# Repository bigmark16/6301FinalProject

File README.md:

# 6301FinalProject
the final project for 6.301. The files included are the eagle schematic file and the brd file used for pcb fab.

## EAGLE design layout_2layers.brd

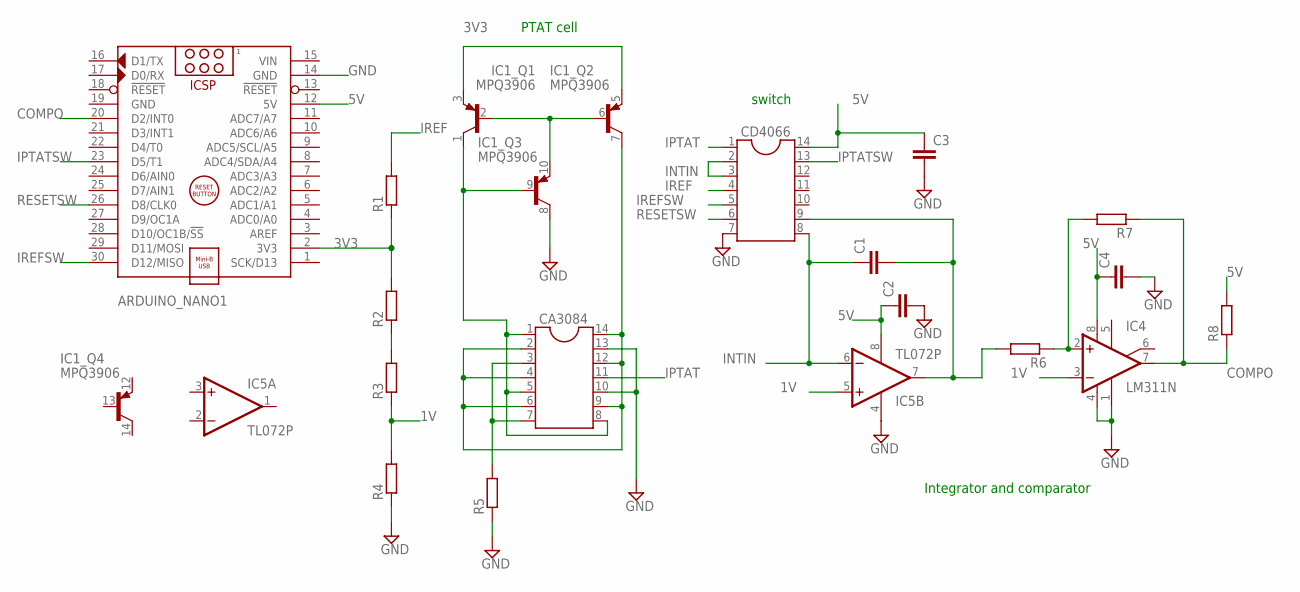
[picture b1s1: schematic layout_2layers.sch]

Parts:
ARDUINO_NANO1: ARDUINO_NANO
C1, C2, C3, C4: C-EU050-025X075; C050-025X075
CA3084: DIL14S; SOCKET-14
CD4066: DIL14S; SOCKET-14
IC1: MPQ3906; DIL14
IC4: LM311N; DIL08
IC5: TL072P; DIL08
R1, R2, R3, R4, R5, R6, R7, R8: R-EU_0207/10; 0207/10

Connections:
1V: IC4.3 (-IN), IC5.5 (+IN), R3.1, R4.2
3V3: ARDUINO_NANO1.2 (3V3), IC1.3 (E), IC1.5 (E), R1.1, R2.2
5V: ARDUINO_NANO1.12 (5V), C2.1, C3.1, C4.1, CD4066.14, IC4.8 (V+), IC5.8 (V+), R8.2
COMPO: ARDUINO_NANO1.20 (D2/INT0), IC4.7 (OUT), R7.1, R8.1
GND: ARDUINO_NANO1.14 (GND), ARDUINO_NANO1.19 (GND), C2.2, C3.2, C4.2, CA3084.10, CA3084.13, CD4066.7, IC1.8 (C), IC4.1 (GND), IC4.4 (V-), IC5.4 (V-), R4.1, R5.1
INTIN: C1.1, CD4066.2, CD4066.3, CD4066.8, IC5.6 (-IN)
IPTAT: CA3084.11, CD4066.1
IPTATSW: ARDUINO_NANO1.23 (D5/T1), CD4066.13
IREF: CD4066.4, R1.2
IREFSW: ARDUINO_NANO1.30 (D12/MISO), CD4066.5
unnamed: CA3084.3, CA3084.7, R5.2
unnamed: CA3084.2, CA3084.4, CA3084.6, CA3084.9, CA3084.12, CA3084.14, IC1.7 (C)
unnamed: IC4.2 (+IN), R6.1, R7.2
unnamed: R2.1, R3.2
unnamed: IC1.2 (B), IC1.6 (B), IC1.10 (E)
unnamed: CA3084.1, CA3084.5, CA3084.8, IC1.1 (C), IC1.9 (B)
RESET2: C1.2, CD4066.9, IC5.7 (OUT), R6.2
RESETSW: ARDUINO_NANO1.26 (D8/CLK0), CD4066.6
VIN: ARDUINO_NANO1.15 (VIN)

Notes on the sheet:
Integrator and comparator
PTAT cell
switch

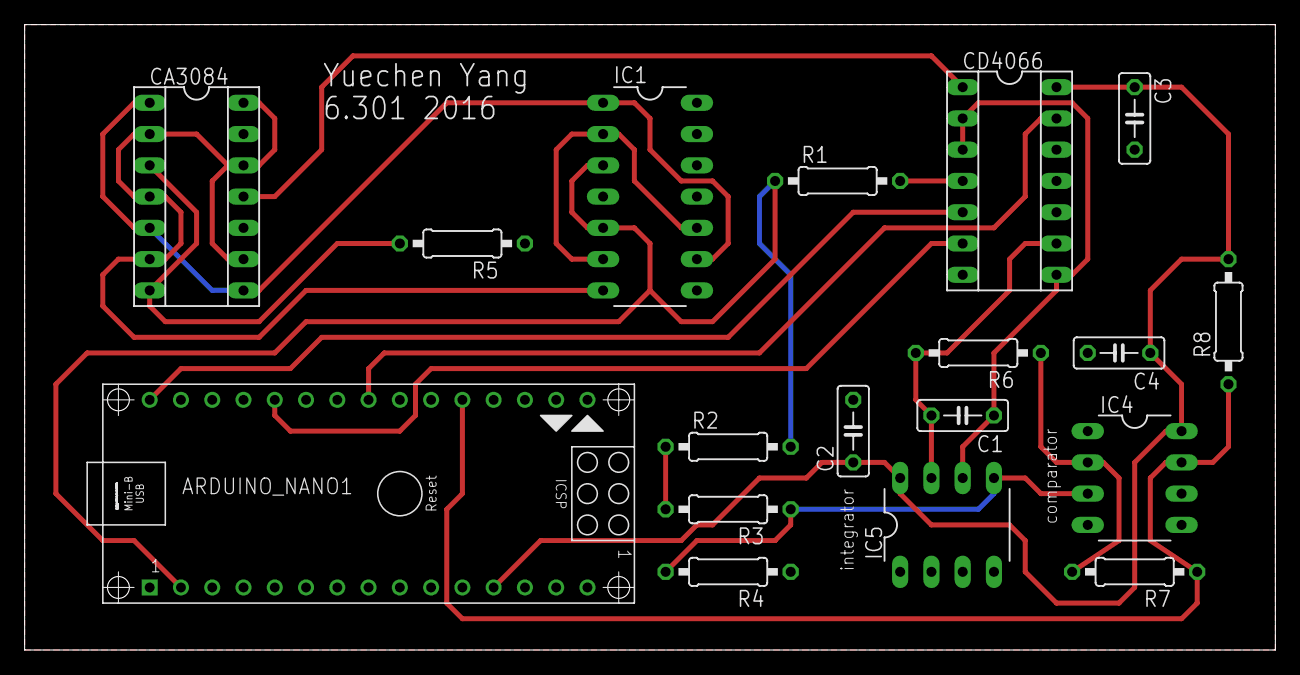
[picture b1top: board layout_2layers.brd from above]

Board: 2 copper layers, 101.6 x 50.8 mm, 18 parts (0 on the bottom side), 18 nets.

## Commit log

2016-12-13 Add files via upload
    The Gerber Files
